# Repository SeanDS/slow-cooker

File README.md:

slow-cooker
===========

Raspberry Pi scripts for controlling a hacked slow cooker.

Schematics for the controller electronics coming later...

Sean Leavey
https://github.com/SeanDS/

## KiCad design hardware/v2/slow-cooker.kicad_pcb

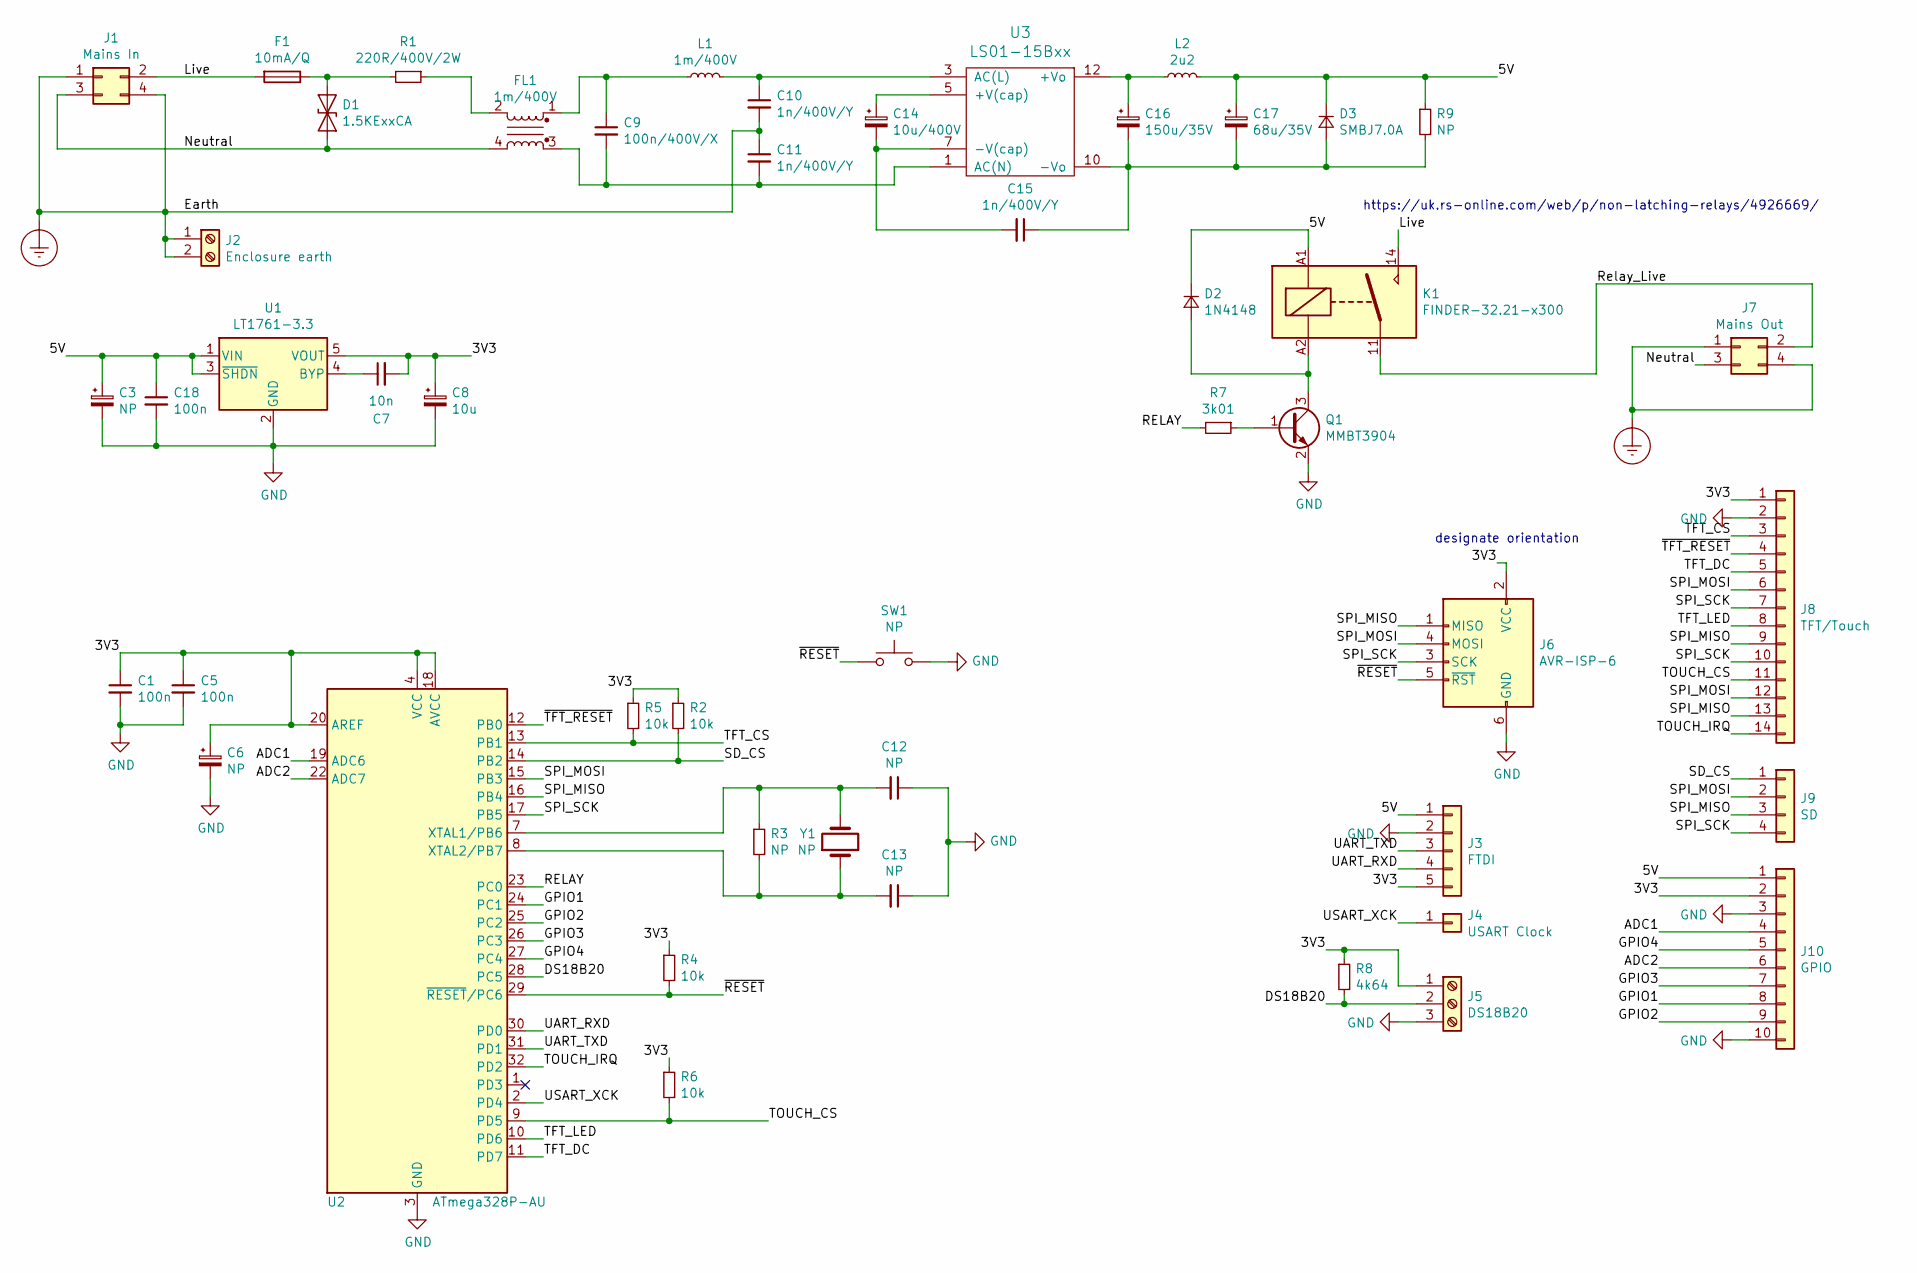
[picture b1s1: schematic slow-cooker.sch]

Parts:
C1, C5, C18: 100n; C_0805_2012Metric_Pad1.15x1.40mm_HandSolder
C3, C6: NP; CP_Radial_D5.0mm_P2.00mm
C7: 10n; C_0805_2012Metric_Pad1.15x1.40mm_HandSolder
C8: 10u; CP_Radial_D5.0mm_P2.00mm
C9: 100n/400V/X; C_Rect_L24_W7.6_P20.3
C10, C11, C15: 1n/400V/Y; C_Rect_L18.0mm_W5.0mm_P15.00mm_FKS3_FKP3
C12, C13: NP; C_0603_1608Metric_Pad1.05x0.95mm_HandSolder
C14: 10u/400V; CP_Radial_D12.5mm_P5.00mm
C16: 150u/35V; CP_Radial_D8.0mm_P3.50mm
C17: 68u/35V; CP_Radial_D6.3mm_P2.50mm
D1: 1.5KExxCA; D_DO-201AE_P15.24mm_Horizontal
D2: 1N4148; D_SMB_Handsoldering
D3: SMBJ7.0A; D_SMB_Handsoldering
F1: 10mA/Q; Wurth_64900001039
FL1: 1m/400V; CommonModeChoke_Epcos-B82730U
J1: Mains In; Molex_Mini-Fit_Jr_5566-04A_2x02_P4.20mm_Vertical
J2: Enclosure earth; TerminalBlock_Phoenix_MKDS-1,5-2-5.08_1x02_P5.08mm_Horizont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
J3: FTDI; PinHeader_1x05_P2.54mm_Vertical
J4: USART Clock; SolderWirePad_1x01_Drill1mm
J5: DS18B20; TerminalBlock_Phoenix_PT-1,5-3-3.5-H_1x03_P3.50mm_Horizontal
J6: AVR-ISP-6; PinHeader_2x03_P2.54mm_Vertical
J7: Mains Out; Molex_Mini-Fit_Jr_5566-04A_2x02_P4.20mm_Vertical
J8: TFT/Touch; PinSocket_1x14_P2.54mm_Vertical
J9: SD; PinSocket_1x04_P2.54mm_Vertical
J10: GPIO; PinHeader_2x05_P2.54mm_Vertical
K1: FINDER-32.21-x300; Relay_SPST_Finder_32.21-x300
L1: 1m/400V; L_Axial_L9.5mm_D4.0mm_P15.24mm_Horizontal_Fastron_SMCC
L2: 2u2; L_0805_2012Metric_Pad1.15x1.40mm_HandSolder
Q1: MMBT3904; SOT-23
R1: 220R/400V/2W; R_Axial_DIN0414_L11.9mm_D4.5mm_P15.24mm_Horizontal
R2, R4, R5, R6: 10k; R_0805_2012Metric_Pad1.15x1.40mm_HandSolder
R3, R9: NP; R_0805_2012Metric_Pad1.15x1.40mm_HandSolder
R7: 3k01; R_0805_2012Metric_Pad1.15x1.40mm_HandSolder
R8: 4k64; R_0805_2012Metric_Pad1.15x1.40mm_HandSolder
SW1: NP; SW_SPST_EVQP0
U1: LT1761-3.3; TSOT-23-5
U2: ATmega328P-AU; TQFP-32_7x7mm_P0.8mm
U3: LS01-15Bxx; Mornsun_LS01-15BxxSS
Y1: NP; Crystal_SMD_HC49-SD

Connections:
/3V3: C1.1, C5.1, C6.1, C7.2, C8.1, J3.5, J5.1, J6.2 (VCC), J8.1, J10.2, R2.1, R4.1, R5.1, R6.1, R8.1, U1.5 (VOUT), U2.4 (VCC), U2.6 (VCC), U2.18 (AVCC), U2.20 (AREF)
/5V: C3.1, C17.1, C18.1, D2.1 (K), D3.1 (K), J3.1, J10.1, K1.A1, L2.2, R9.1, U1.1 (VIN), U1.3 (~SHDN)
/ADC1: J10.4, U2.19 (ADC6)
/ADC2: J10.6, U2.22 (ADC7)
/DS18B20: J5.2, R8.2, U2.28 (PC5)
/GPIO1: J10.8, U2.24 (PC1)
/GPIO2: J10.9, U2.25 (PC2)
/GPIO3: J10.7, U2.26 (PC3)
/GPIO4: J10.5, U2.27 (PC4)
/Live: F1.2, J1.2, K1.14
/Neutral: D1.2 (A2), FL1.4, J1.3, J7.3
/RELAY: R7.2, U2.23 (PC0)
/Relay_Live: J7.2, K1.11
/SD_CS: J9.1, R2.2, U2.14 (PB2)
/SPI_MISO: J6.1 (MISO), J8.9, J8.13, J9.3, U2.16 (PB4)
/SPI_MOSI: J6.4 (MOSI), J8.6, J8.12, J9.2, U2.15 (PB3)
/SPI_SCK: J6.3 (SCK), J8.7, J8.10, J9.4, U2.17 (PB5)
/TFT_CS: J8.3, R5.2, U2.13 (PB1)
/TFT_DC: J8.5, U2.11 (PD7)
/TFT_LED: J8.8, U2.10 (PD6)
/TOUCH_CS: J8.11, R6.2, U2.9 (PD5)
/TOUCH_IRQ: J8.14, U2.32 (PD2)
/UART_RXD: J3.4, U2.30 (PD0)
/UART_TXD: J3.3, U2.31 (PD1)
/USART_XCK: J4.1, U2.2 (PD4)
/~RESET: J6.5 (~RST), R4.2, SW1.1, U2.29 (~RESET~/PC6)
/~TFT_RESET: J8.4, U2.12 (PB0)
Earth_Protective: C10.2, C11.1, J1.1, J1.4, J2.1, J2.2, J7.1, J7.4
GND: C1.2, C3.2, C5.2, C6.2, C8.2, C12.1, C13.1, C18.2, J3.2, J5.3, J6.6 (GND), J8.2, J10.3, J10.10, Q1.2 (E), SW1.2, U1.2 (GND), U2.3 (GND), U2.5 (GND), U2.21 (GND)
unnamed: C7.1, U1.4 (BYP)
unnamed: C9.1, FL1.1, L1.1
unnamed: C10.1, L1.2, U3.3 (AC(L))
unnamed: C9.2, C11.2, FL1.3, U3.1 (AC(N))
unnamed: C12.2, R3.1, U2.7 (XTAL1/PB6), Y1.2
unnamed: C13.2, R3.2, U2.8 (XTAL2/PB7), Y1.1
unnamed: C14.1, U3.5 (+V(cap))
unnamed: C14.2, C15.2, U3.7 (-V(cap))
unnamed: C15.1, C16.2, C17.2, D3.2 (A), R9.2, U3.10 (-Vo)
unnamed: C16.1, L2.1, U3.12 (+Vo)
unnamed: D1.1 (A1), F1.1, R1.2
unnamed: D2.2 (A), K1.A2, Q1.3 (C)
unnamed: FL1.2, R1.1
unnamed: Q1.1 (B), R7.1

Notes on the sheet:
designate orientation
https://uk.rs-online.com/web/p/non-latching-relays/4926669/

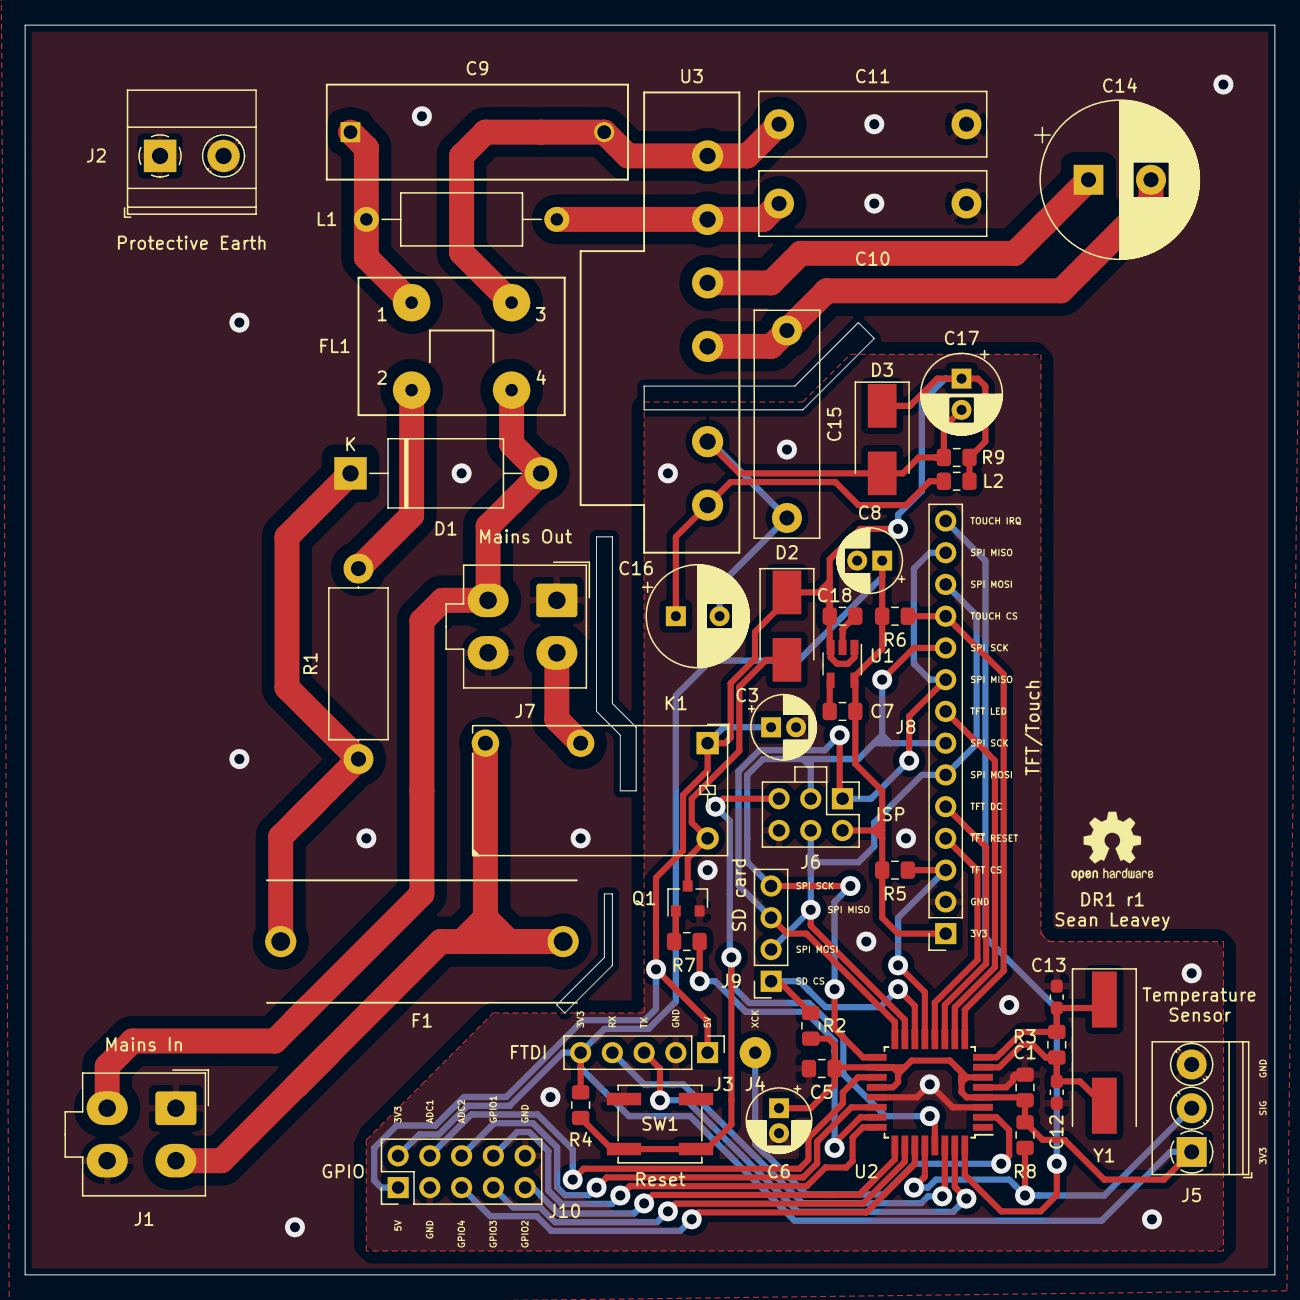
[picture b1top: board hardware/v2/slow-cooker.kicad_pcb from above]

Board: 2 copper layers, 100.0 x 100.0 mm, 50 parts (0 on the bottom side), 43 nets.

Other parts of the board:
Ref**: 100mmx100mm

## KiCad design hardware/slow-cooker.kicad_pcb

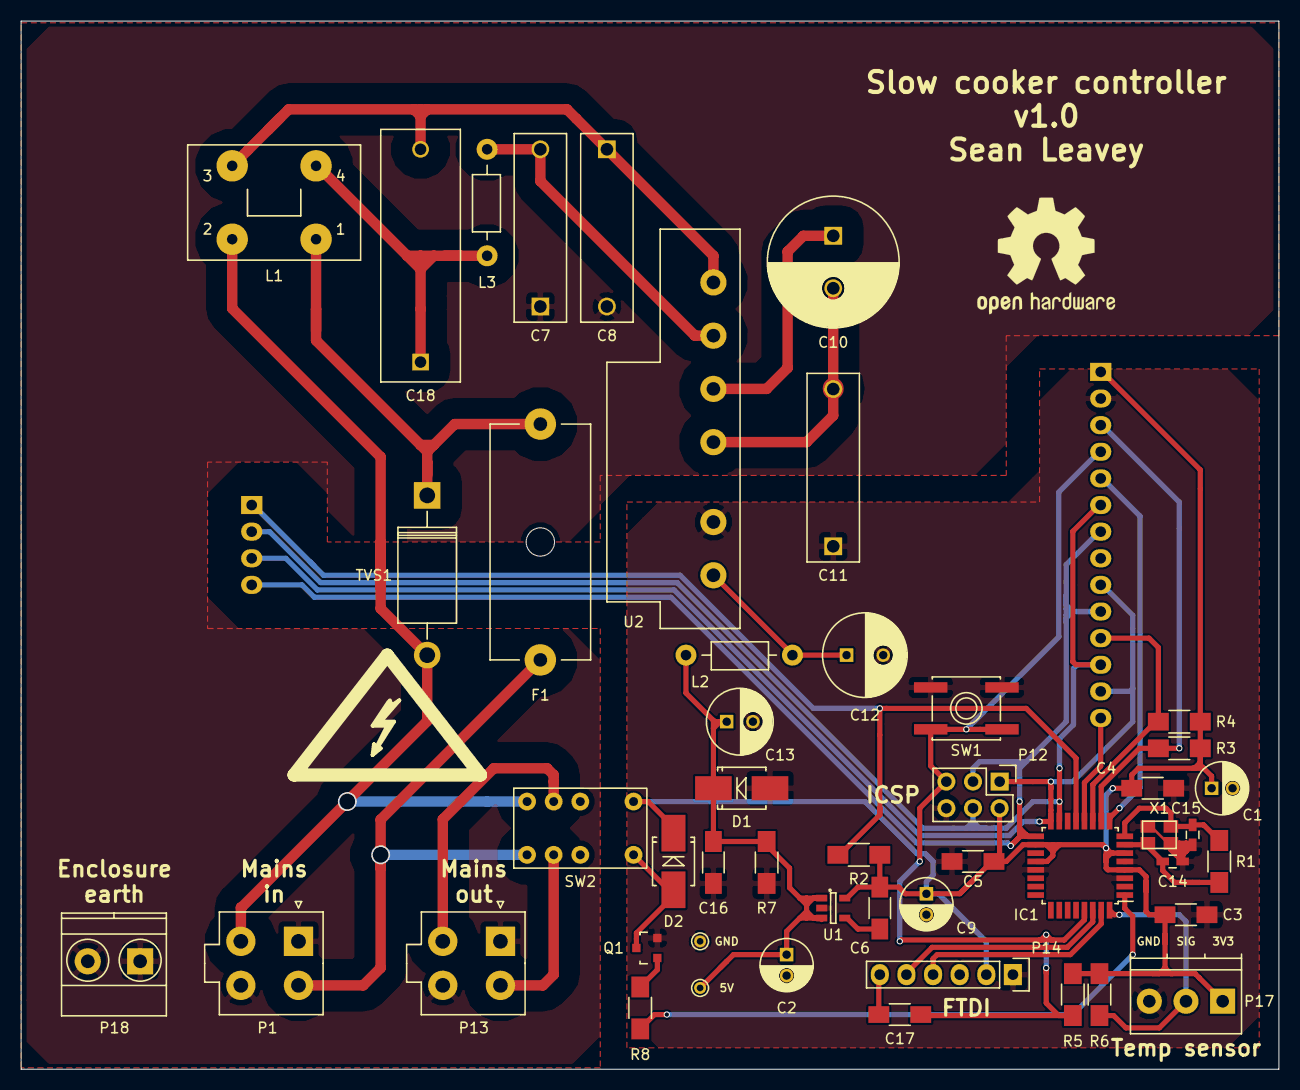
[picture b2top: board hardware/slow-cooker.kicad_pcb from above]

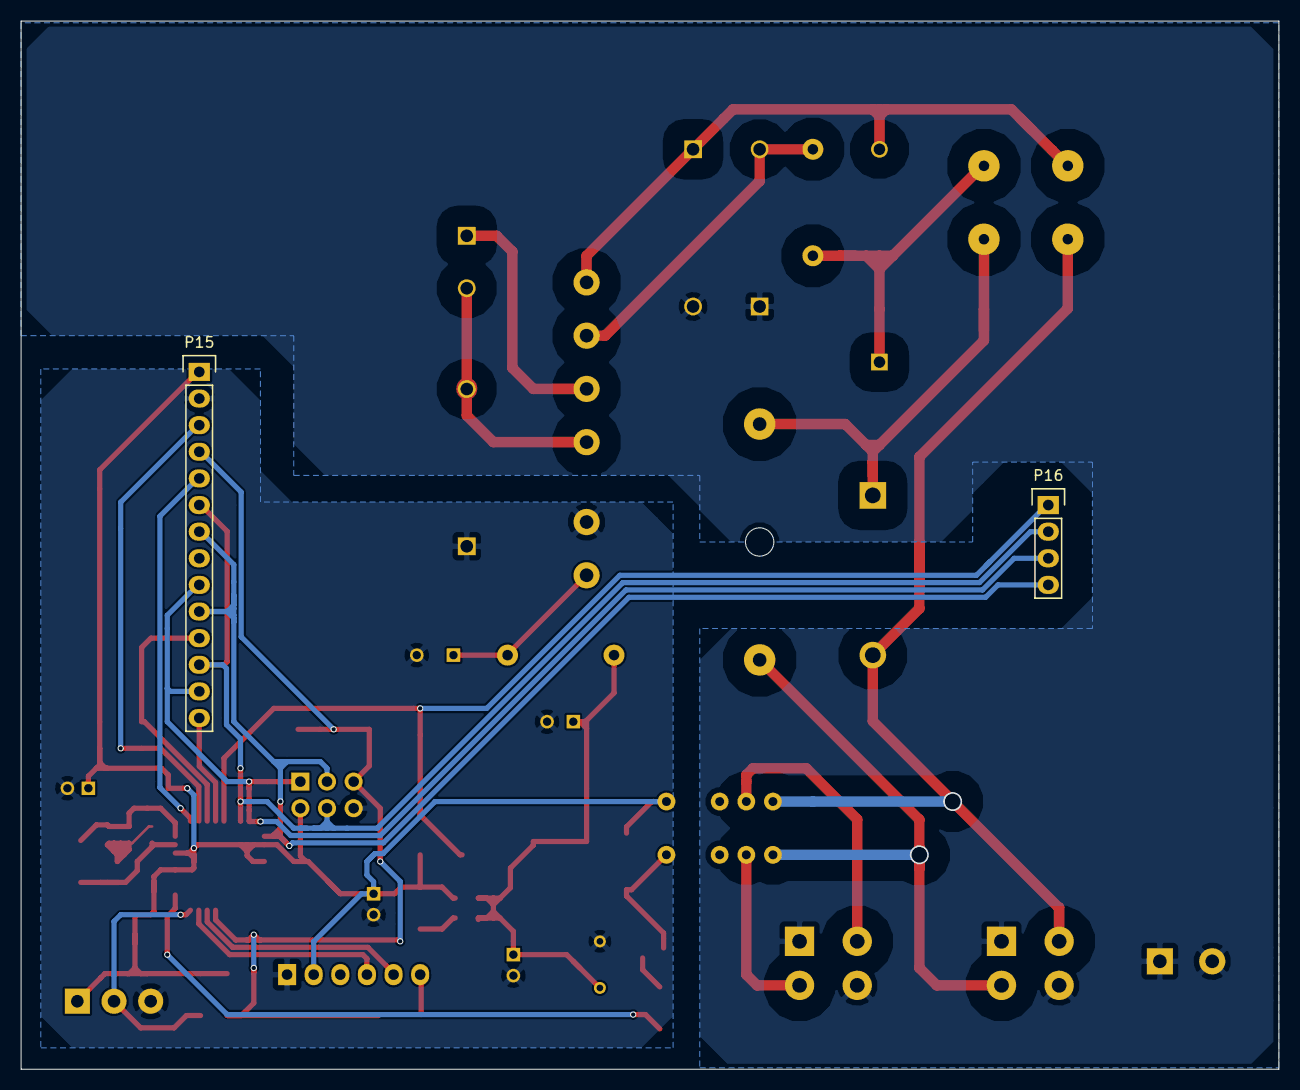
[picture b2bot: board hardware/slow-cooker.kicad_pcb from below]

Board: 2 copper layers, 120.0 x 100.0 mm, 51 parts (2 on the bottom side), 34 nets.

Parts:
C1, C2, C9: 10u; C_Radial_D5_L11_P2
C3, C4, C5, C6: 10n; C_1206_HandSoldering
C7, C8, C11: 1n/400V/Y; C_Rect_L18_W5_P15
C10: 10u/400V; C_Radial_D12.5_L25_P5
C12: 150u; C_Radial_D8_L11.5_P3.5
C13: 68u; C_Radial_D6.3_L11.2_P2.5
C14, C15: 12p; C_0603_HandSoldering
C16, C17: 100n; C_1206_HandSoldering
C18: 100n/400V/X; C_Rect_L24_W7.6_P20.3
D1: SMBJ7.0A; SMB_Handsoldering
D2: STTH212U; SMB_Handsoldering
F1: 10mA, Q; Fuseholder5x20_horiz_open_Schurter_0031_8201
IC1: ATMEGA328-AN; TQFP-32_7x7mm_Pitch0.8mm
L1: 1m/400V; CommonModeChoke_Epcos-B82730U
L2: 2.2u; Choke_Horizontal_RM10mm
L3: 1m/400V; Choke_Horizontal_RM10mm
P1: Input; Molex_MiniFit-JR-5556-04A_2x02x4.20mm_Straight
P10: TEST_5V; PINTST
P11: TEST_GND; PINTST
P12: ICSP; Pin_Header_Straight_2x03
P13: Output; Molex_MiniFit-JR-5556-04A_2x02x4.20mm_Straight
P14: FTDI; Pin_Header_Straight_1x06
P15: LCD 1; Pin_Header_Straight_1x14
P16: LCD 2; Pin_Header_Straight_1x04
P17: Temperature sensor; TerminalBlock_Pheonix_PT-3.5mm_3pol
P18: Enclosure earth; TerminalBlock_Pheonix_MKDS1.5-2pol
Q1: MMBT3904; SOT-23
R1: 1M; R_1206_HandSoldering
R2, R3, R4, R5, R8: 10k; R_1206_HandSoldering
R6: 4k7; R_1206_HandSoldering
R7: NP; R_1206_HandSoldering
Ref**: Val**; 100mmx120mm
SW1: Reset; SW_SPST_EVQP0
SW2: TE D3223; FX2 D3223
TVS1: 1.5KE300CA1; Diode_DO-201AD_Horizontal_RM15
U1: LT1761-3.3; SOT-23-5
U2: LS01-15B05S; RS_Pro_LS01
X1: 16MHz; crystal_FA238-TSX3225

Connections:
/3V3: C1.1, C3.2, C4.2, C5.2, C6.1, C9.1, D2.1, IC1.4, IC1.6, IC1.18, IC1.20, P12.2, P14.2, P15.1, P17.1, R2.1, R3.1, R4.1, R5.1, R6.1, SW2.1, U1.5
/5V: C2.1, C13.1, C16.1, D1.1, L2.2, P10.1, R7.1, U1.1, U1.3
/DS18B20: IC1.32, P17.2, R6.2
/Live: F1.1, P1.2, SW2.6
/Neutral: L1.2, P1.3, SW2.5, TVS1.2
/RELAY: IC1.1, R8.2
/Relay_Live: P13.2, SW2.7
/Relay_Neutral: P13.3, SW2.4
/SD_CS: IC1.13, P16.1, R2.2
/SPI_MISO: IC1.16, P12.1, P15.9, P15.13, P16.3
/SPI_MOSI: IC1.15, P12.4, P15.6, P15.12, P16.2
/SPI_SCK: IC1.17, P12.3, P15.7, P15.10, P16.4
/TFT_CS: IC1.10, P15.3, R3.2
/TFT_D/C: IC1.9, P15.5
/T_CS: IC1.11, P15.11, R4.2
/T_IRQ: IC1.12, P15.14
/USART_RXD: IC1.30, P14.5
/USART_TXD: IC1.31, P14.4
/~RESET: C17.1, IC1.29, P12.5, P15.4, R5.2, SW1.1
Earth_Protective: C7.1, C8.2, P1.1, P1.4, P13.1, P13.4, P18.1, P18.2
GND: C1.2, C2.2, C3.1, C4.1, C5.1, C9.2, C11.1, C12.2, C13.2, C14.2, C15.2, C16.2, D1.2, IC1.3, IC1.5, IC1.21, P11.1, P12.6, P14.1, P15.2, P17.3, Q1.2, R7.2, SW1.2, U1.2, U2.10, X1.3
unnamed: C6.2, U1.4
unnamed: C7.2, L3.2, U2.3
unnamed: C10.1, U2.5
unnamed: C10.2, C11.2, U2.7
unnamed: C12.1, L2.1, U2.12
unnamed: C14.1, IC1.7, R1.1, X1.2
unnamed: C15.1, IC1.8, R1.2, X1.1
unnamed: C17.2, P14.6
unnamed: C18.1, L1.4, L3.1
unnamed: C8.1, C18.2, L1.3, U2.1
unnamed: D2.2, Q1.3, SW2.10
unnamed: F1.2, L1.1, TVS1.1
unnamed: Q1.1, R8.1

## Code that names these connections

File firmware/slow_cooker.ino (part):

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#endif

#ifndef ONE_WIRE_BUS_PIN
  #define ONE_WIRE_BUS_PIN      A5 // DS18B20 data
#endif

// DS18B20 temperature precision: 9 (93.8ms), 10 (187.5ms), 11 (375ms) or 12 (750ms) bits
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  #define BUTTON_DEBOUNCE_DELAY 500
#endif

#ifndef TFT_DC_PIN
  #define TFT_DC_PIN 7
#endif

#ifndef TFT_CS_PIN
  #define TFT_CS_PIN 9
#endif

#ifndef TFT_RESET_PIN
  #define TFT_RESET_PIN 8
#endif

#ifndef TFT_BACKLIGHT_PIN
  #define TFT_BACKLIGHT_PIN 6
#endif

#ifndef TOUCH_CS_PIN
  #define TOUCH_CS_PIN 5
#endif

#ifndef TOUCH_IRQ_PIN
  #define TOUCH_IRQ_PIN 2
#endif

#include <Arduino.h>
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 * TFT screen.
 */

Ucglib_ILI9341_18x240x320_HWSPI ucg(/*cd=*/ TFT_DC_PIN, /*cs=*/ TFT_CS_PIN);

// Flag for whether to redraw the screen in the loop.
bool redraw_screen;
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 * Touch screen.
 */

XPT2046 touch(/*cs=*/ TOUCH_CS_PIN, /*irq=*/ TOUCH_IRQ_PIN);

// Current x and y touch coordinates.
static uint16_t touch_x = 0xffff;
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  // I/O.
  pinMode(POWER_RELAY_PIN, OUTPUT);
  digitalWrite(POWER_RELAY_PIN, LOW);
  pinMode(TFT_RESET_PIN, OUTPUT);
  digitalWrite(TFT_RESET_PIN, HIGH); // active LOW
  pinMode(TFT_BACKLIGHT_PIN, OUTPUT); // TFT LED
  digitalWrite(TFT_BACKLIGHT_PIN, HIGH);

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
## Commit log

2017-07-24 Preliminary schematic
2017-07-26 First enclosure attempt
2017-08-20 Board layout
2019-05-07 Move v1
2019-05-07 Add v2
2020-10-25 Add test firmware
